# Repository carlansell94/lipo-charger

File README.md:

LiPo battery chargers based on the Adafruit MicroLipo, with added reverse polarity protection.

Features:
* Based on a proven and tested design by Adafruit.
* Includes JST-PH and JST-ZH footprints to support a wider range of battery connectors.
* v1 supports 1x JST-PH port and 1x JST-ZH port, while v2 has 2 of each port - the second pair on the rear swapping the polarity of the connector.
* Includes an additional output port for batteries using a JST-PZ connector.
* Reverse polarity protection for the charging IC, useful if you're dealing with batteries with the wires switched around (such as a Dualshock 4 battery).
* v2 features a USB type C port for power input, and a surface-mount switch to choose between fast and slow charging modes (v1 required soldering a resistor).

Note that you MUST NOT try to use multiple ports at once, this board is only designed to charge one battery at a time.

The original Adafruit design can be found [here](https://learn.adafruit.com/adafruit-microlipo-and-minilipo-battery-chargers/downloads).

Included in this repository are the KiCAD files for both designs. If you're only interested in having them manufactured, gerbers are available under 'releases'.

## Parts Lists
v1 Parts List:
| Component                       |Qty| Symbol(s) |
| ------------------------------- | - | --------- |
| USB Micro B Port                | 1 | X1        |
| MCP73831/2 SOT23 Charging IC    | 1 | U1        |
| 0805 10uF Capacitor             | 2 | C1,C2     |
| 0805 470Ω Resistor              | 2 | R1,R2     |
| 0805 10kΩ Resistor              | 1 | R3        |
| 0805 2.49kΩ Resistor            | 1 | R4        |
| 0805 100kΩ Resistor             | 1 | R5        |
| 0805 1MΩ Resistor               | 1 | R6        |
| ZXMP3A13FTA P Channel MOSFET    | 1 | Q1        |
| MMBT3904,215 BJT NPN Transistor | 1 | Q2        |
| 0805 LED (Colours Optional)     | 2 | LED1,LED2 |
| JST-PH Connector                | 1 | CN1       |
| JST-PZ Connector                | 1 | CN2       | (Optional)
| 0805 0Ω Resistor                | 1 | SJ1       | (Optional)

v2 Parts List:
| Component                       |Qty| Symbol(s) |
| ------------------------------- | - | --------- |
| 16-pin USB Type C Port          | 1 | J1        |
| MCP73831/2 SOT23 Charging IC    | 1 | U1        |
| 0805 10uF Capacitor             | 2 | C1,C2     |
| 0805 470Ω Resistor              | 2 | R1,R2     |
| 0805 10kΩ Resistor              | 1 | R3        |
| 0805 2kΩ Resistor               | 1 | R4        |
| 0805 100kΩ Resistor             | 1 | R5        |
| 0805 1MΩ Resistor               | 1 | R6        |
| 0805 5.1kΩ Resistor             | 2 | R7,R8     | (Optional)
| ZXMP3A13FTA P Channel MOSFET    | 1 | Q1        |
| MMBT3904,215 BJT NPN Transistor | 1 | Q2        |
| 0805 LED (Colours Optional)     | 2 | LED1,LED2 |
| JST-PH Connector                | 2 | CN1,CN4   |
| JST-PZ Connector                | 1 | CN2,CN3   | (Optional)
| PCM12SMTR Slide Switch          | 1 | SW1       | (Optional)

For more information on the v1 (micro USB) board, take a look at [my blog post](https://qubitsandbytes.co.uk/lipo-charger-with-reverse-polarity-protection/).

For more information on the v2 (USB type C) board, take a look at [this post](https://qubitsandbytes.co.uk/building-a-better-lipo-battery-charger/).

## Images
v1 KiCAD render:

v2 KiCAD render:

## KiCAD
The files in this project were created using KiCAD. To open these files, make sure you're using KiCAD v9 or above.

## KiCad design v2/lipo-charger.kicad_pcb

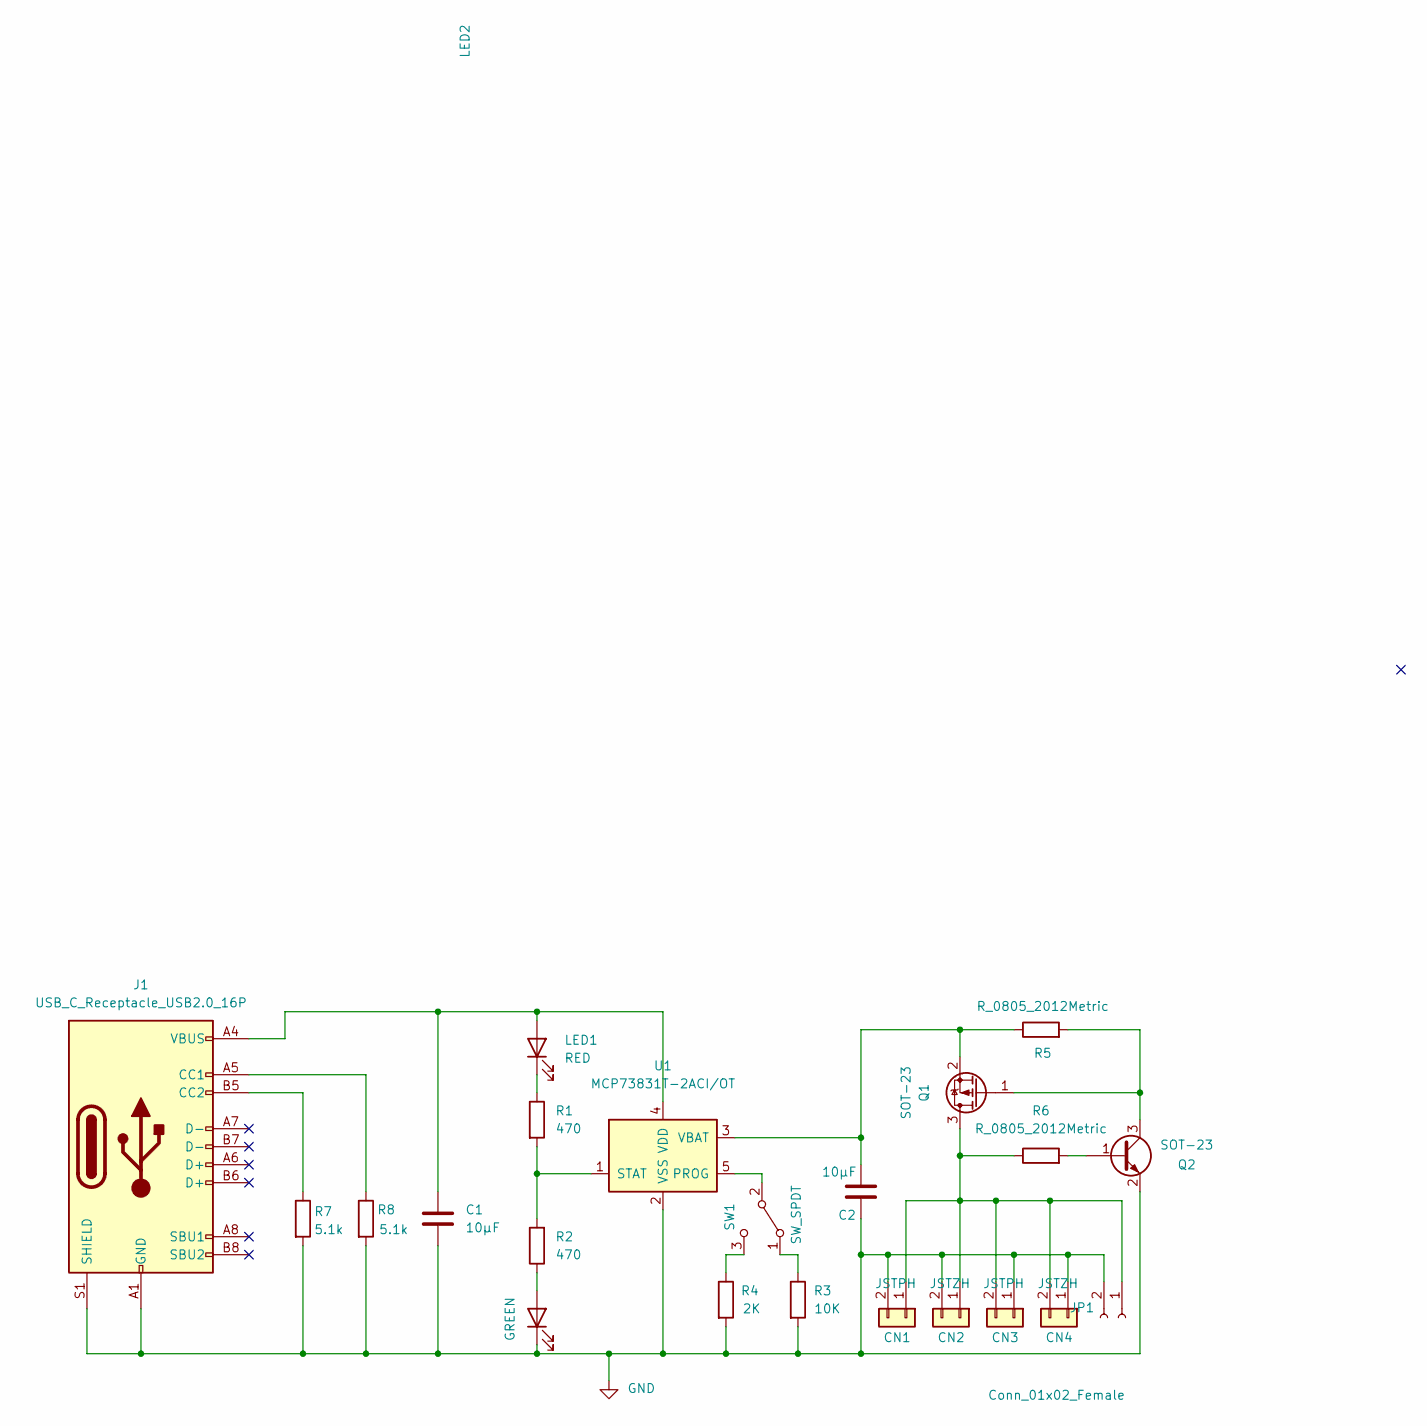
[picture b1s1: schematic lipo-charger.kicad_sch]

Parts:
C1, C2: 10µF; C_0805_2012Metric
CN1, CN3: JSTPH; JST_PH_S2B-PH-SM4-TB_1x02-1MP_P2.00mm_Horizontal
CN2, CN4: JSTZH; JST_ZH_S2B-ZR-SM4A-TF_1x02-1MP_P1.50mm_Horizontal
J1: USB_C_Receptacle_USB2.0_16P; USB_C_Receptacle_HRO_TYPE-C-31-M-12
JP1: Conn_01x02_Female; PinHeader_1x02_P2.54mm_Vertical
LED1: RED; LED_0805_2012Metric
LED2: GREEN; LED_0805_2012Metric
Q1, Q2: SOT-23
R1, R2: 470; R_0805_2012Metric
R3: 10K; R_0805_2012Metric
R4: 2K; R_0805_2012Metric
R5, R6: R_0805_2012Metric
R7, R8: 5.1k; R_0603_1608Metric
SW1: SW_SPDT; SW_SPDT_PCM12
U1: MCP73831T-2ACI/OT; SOT-23-5

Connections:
GND: C1.2, C2.2, CN1.2, CN1.MP, CN2.2, CN2.MP, CN3.1, CN3.MP, CN4.1, CN4.MP, J1.A1 (GND), J1.A12 (GND), J1.B1 (GND), J1.B12 (GND), J1.S1 (SHIELD), JP1.2, LED2.1 (K), Q2.2 (E), R3.2, R4.2, R7.2, R8.2, U1.2 (VSS)
unnamed: CN1.1, CN2.1, CN3.2, CN4.2, JP1.1, Q1.3 (D), R6.1
unnamed: J1.A5 (CC1), R8.1
unnamed: J1.B5 (CC2), R7.1
unnamed: C1.1, J1.A4 (VBUS), J1.A9 (VBUS), J1.B4 (VBUS), J1.B9 (VBUS), LED1.2 (A), U1.4 (VDD)
unnamed: LED1.1 (K), R1.1
unnamed: LED2.2 (A), R2.1
unnamed: Q1.1 (G), Q2.3 (C), R5.2
unnamed: C2.1, Q1.2 (S), R5.1, U1.3 (VBAT)
unnamed: Q2.1 (B), R6.2
unnamed: R3.1, SW1.1 (A)
unnamed: SW1.2 (B), U1.5 (PROG)
unnamed: R4.1, SW1.3 (C)
unnamed: R1.2, R2.2, U1.1 (STAT)

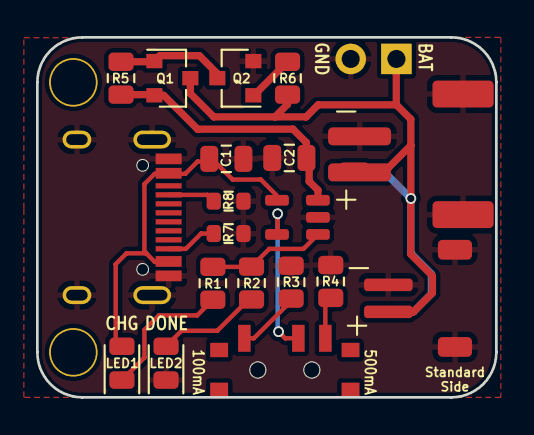
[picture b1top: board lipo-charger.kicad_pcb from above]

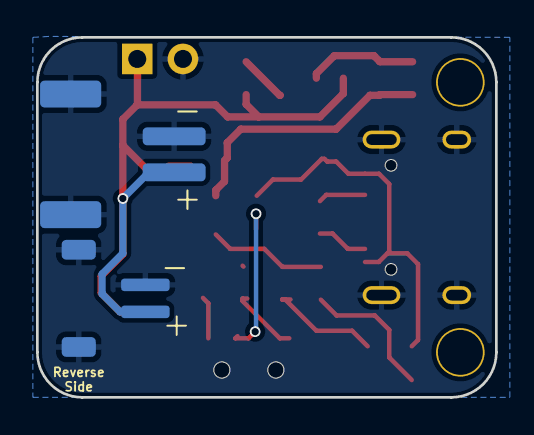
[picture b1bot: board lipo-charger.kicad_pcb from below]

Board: 2 copper layers, 25.5 x 20.0 mm, 24 parts (2 on the bottom side), 14 nets.

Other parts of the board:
H1, H2: MountingHole_2.5mm

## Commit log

2025-08-30 chore: Add .gitignore
2025-08-30 chore: Move original version into v1 folder
2025-08-30 feat: Add v2 files
2025-08-30 docs: Update readme
